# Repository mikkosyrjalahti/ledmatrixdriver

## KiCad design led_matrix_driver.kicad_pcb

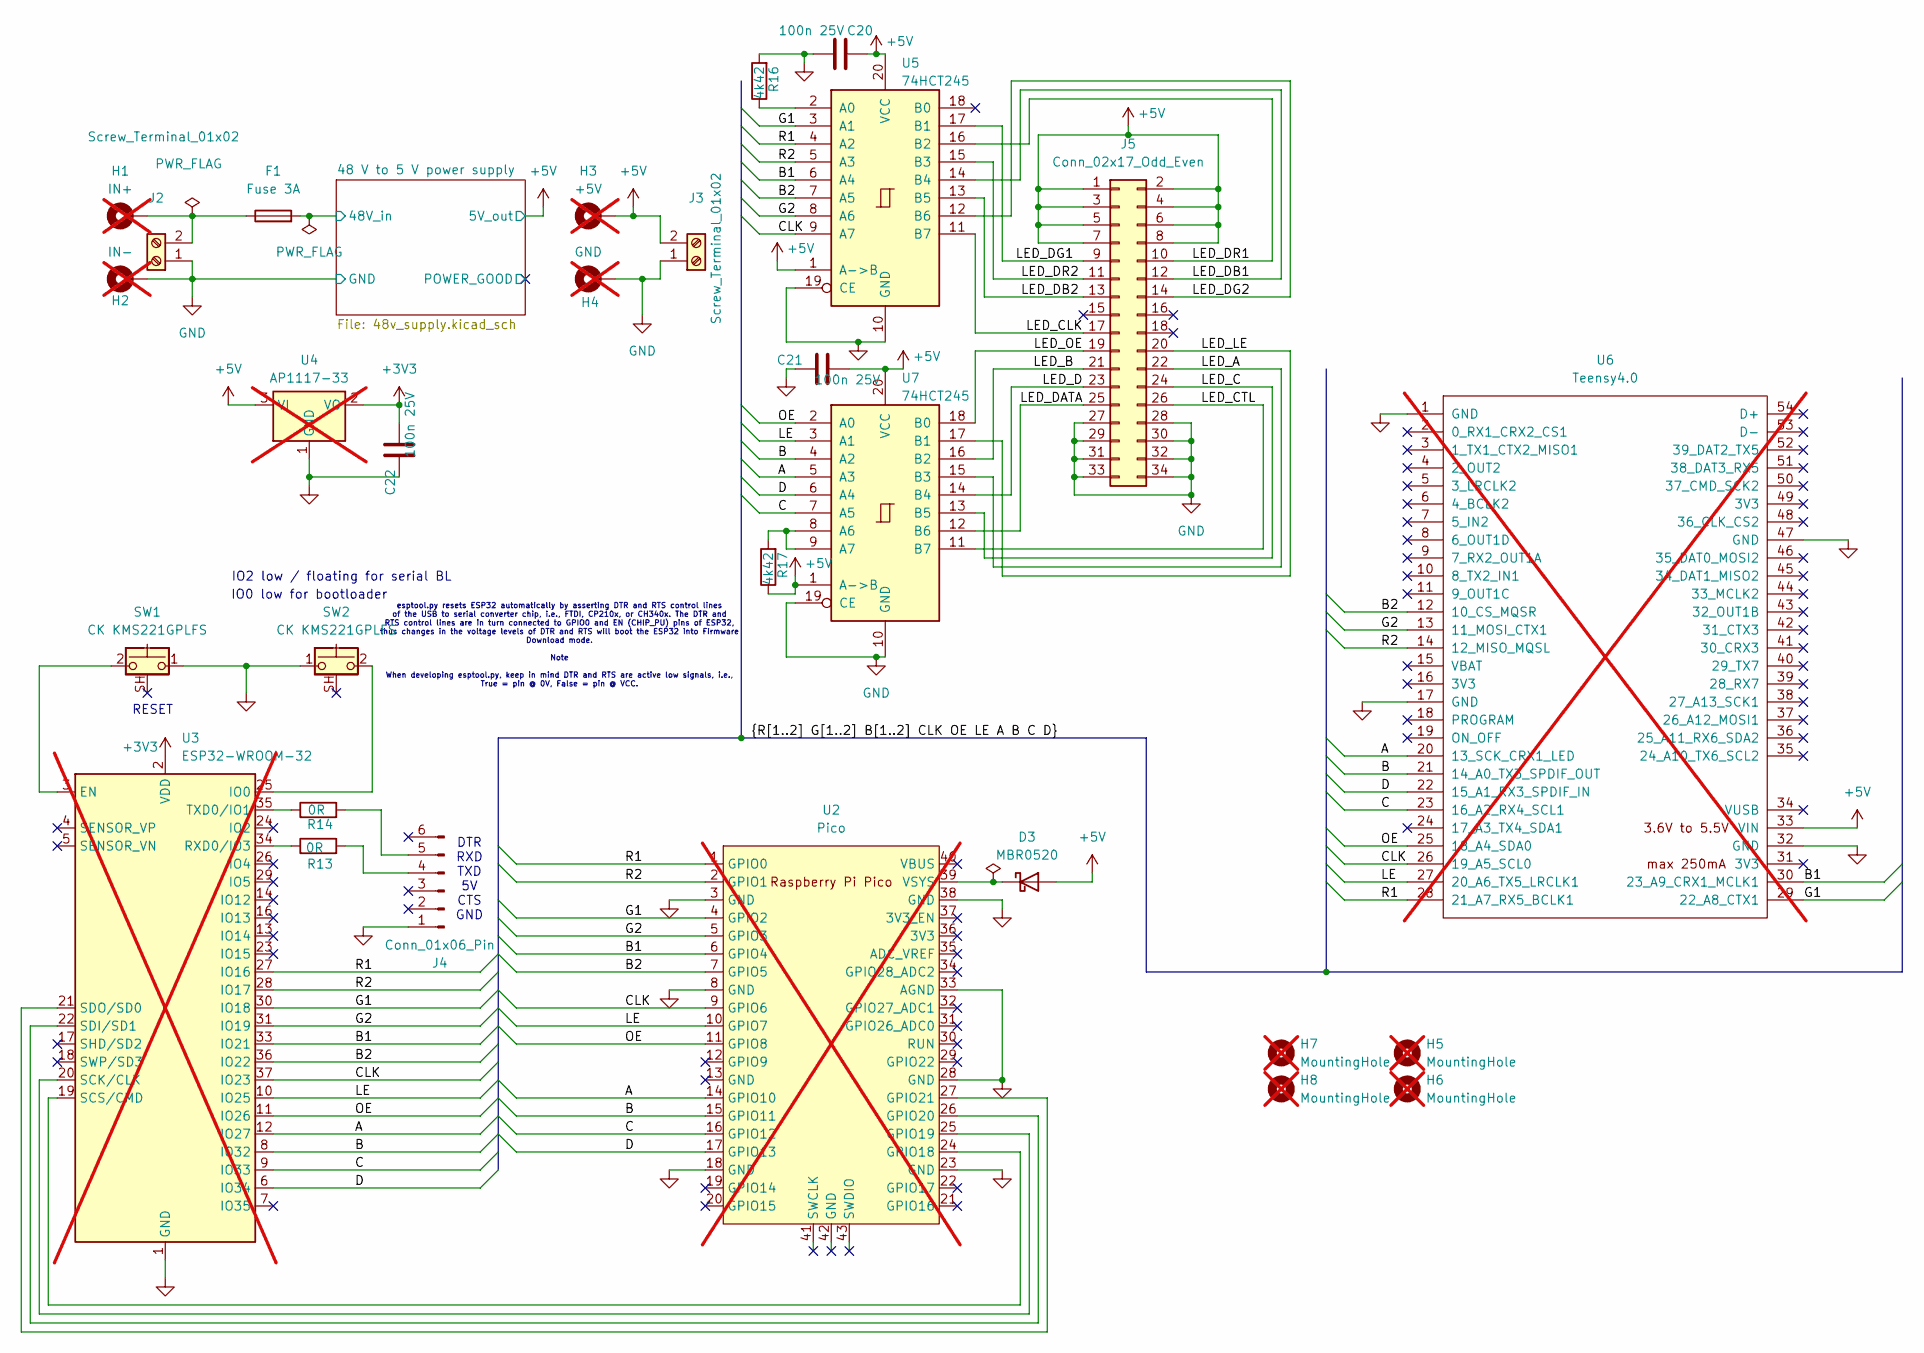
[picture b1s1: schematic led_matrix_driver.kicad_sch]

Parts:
C20, C21, C22: 100n 25V; C_0805_2012Metric; LCSC C28233
D3: MBR0520; D_SOD-123; LCSC C78545
F1: Fuse 3A; Fuseholder_Littelfuse_Nano2_154x; LCSC C206912
H1: IN+; MountingHole_2.2mm_M2_DIN965_Pad; not fitted
H2: IN-; MountingHole_2.2mm_M2_DIN965_Pad; not fitted
H3: +5V; MountingHole_2.2mm_M2_DIN965_Pad; not fitted
H4: GND; MountingHole_2.2mm_M2_DIN965_Pad; not fitted
H5, H6, H7, H8: MountingHole; MountingHole_3.2mm_M3; not fitted
J2, J3: Screw_Terminal_01x02; Samtec_HPM-02-01-x-S_Straight_1x02_Pitch5.08mm
J4: Conn_01x06_Pin; PinHeader_1x06_P2.54mm_Vertical
J5: Conn_02x17_Odd_Even; PinSocket_2x17_P2.54mm_Vertical
R13, R14: 0R; R_0603_1608Metric
R16, R17: 4k42; R_0603_1608Metric; LCSC C2933223
SW1, SW2: CK KMS221GPLFS; SW_SPST_CK_KMS2xxGP
U2: Pico; RPi_Pico_SMD_TH; not fitted
U3: ESP32-WROOM-32; not fitted
U4: AP1117-33; SOT-223-3_TabPin2; not fitted
U5, U7: 74HCT245; SOIC-20W_7.5x12.8mm_P1.27mm; LCSC C94773
U6: Teensy4.0; Teensy40_SMT; not fitted

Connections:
+3V3: C22.2, U3.2 (VDD), U4.2 (VO)
+5V: C20.2, C21.2, D3.2 (A), H3.1, J3.2, J5.1, J5.2, J5.3, J5.4, J5.5, J5.6, J5.7, J5.8, R17.1, U4.3 (VI), U5.1 (A->B), U5.20 (VCC), U6.33 (VIN), U7.1 (A->B), U7.20 (VCC); also elsewhere on the board
/48 V to 5 V power supply/48V_in: F1.2; also elsewhere on the board
/A: U2.14 (GPIO10), U3.12 (IO27), U6.20 (13_SCK_CRX1_LED), U7.5 (A3)
/B: U2.15 (GPIO11), U3.8 (IO32), U6.21 (14_A0_TX3_SPDIF_OUT), U7.4 (A2)
/B1: U2.6 (GPIO4), U3.33 (IO21), U5.6 (A4), U6.30 (23_A9_CRX1_MCLK1)
/B2: U2.7 (GPIO5), U3.36 (IO22), U5.7 (A5), U6.12 (10_CS_MQSR)
/C: U2.16 (GPIO12), U3.9 (IO33), U6.23 (16_A2_RX4_SCL1), U7.7 (A5)
/CLK: U2.9 (GPIO6), U3.37 (IO23), U5.9 (A7), U6.26 (19_A5_SCL0)
/D: U2.17 (GPIO13), U3.6 (IO34), U6.22 (15_A1_RX3_SPDIF_IN), U7.6 (A4)
/G1: U2.4 (GPIO2), U3.30 (IO18), U5.3 (A1), U6.29 (22_A8_CTX1)
/G2: U2.5 (GPIO3), U3.31 (IO19), U5.8 (A6), U6.13 (11_MOSI_CTX1)
/LE: U2.10 (GPIO7), U3.10 (IO25), U6.27 (20_A6_TX5_LRCLK1), U7.3 (A1)
/LED_A: J5.22, U7.15 (B3)
/LED_B: J5.21, U7.16 (B2)
/LED_C: J5.24, U7.13 (B5)
/LED_CLK: J5.17, U5.11 (B7)
/LED_CTL: J5.26, U7.11 (B7)
/LED_D: J5.23, U7.14 (B4)
/LED_DATA: J5.25, U7.12 (B6)
/LED_DB1: J5.12, U5.14 (B4)
/LED_DB2: J5.13, U5.13 (B5)
/LED_DG1: J5.9, U5.17 (B1)
/LED_DG2: J5.14, U5.12 (B6)
/LED_DR1: J5.10, U5.16 (B2)
/LED_DR2: J5.11, U5.15 (B3)
/LED_LE: J5.20, U7.17 (B1)
/LED_OE: J5.19, U7.18 (B0)
/OE: U2.11 (GPIO8), U3.11 (IO26), U6.25 (18_A4_SDA0), U7.2 (A0)
/R1: U2.1 (GPIO0), U3.27 (IO16), U5.4 (A2), U6.28 (21_A7_RX5_BCLK1)
/R2: U2.2 (GPIO1), U3.28 (IO17), U5.5 (A3), U6.14 (12_MISO_MQSL)
GND: C20.1, C21.1, C22.1, H2.1, H4.1, J2.1, J3.1, J4.1, J5.27, J5.28, J5.29, J5.30, J5.31, J5.32, J5.33, J5.34, R16.2, SW1.1, SW2.1, U2.3 (GND), U2.8 (GND), U2.18 (GND), U2.23 (GND), U2.28 (GND), U2.33 (AGND), U2.38 (GND), U3.1 (GND), U3.15 (GND), U3.38 (GND), U3.39 (GND), U4.1 (GND), U5.10 (GND), U5.19 (CE), U6.1 (GND), U6.17 (GND), U6.32 (GND), U6.47 (GND), U7.10 (GND), U7.19 (CE); also elsewhere on the board
unnamed: D3.1 (K), U2.39 (VSYS)
unnamed: F1.1, H1.1, J2.2
unnamed: J4.4, R13.2
unnamed: J4.5, R14.2
unnamed: U2.24 (GPIO18), U3.19 (SCS/CMD)
unnamed: U2.25 (GPIO19), U3.20 (SCK/CLK)
unnamed: U2.26 (GPIO20), U3.22 (SDI/SD1)
unnamed: U2.27 (GPIO21), U3.21 (SDO/SD0)
unnamed: SW1.2, U3.3 (EN)
unnamed: SW2.2, U3.25 (IO0)
unnamed: R13.1, U3.34 (RXD0/IO3)
unnamed: R14.1, U3.35 (TXD0/IO1)
unnamed: R16.1, U5.2 (A0)
unnamed: R17.2, U7.8 (A6), U7.9 (A7)

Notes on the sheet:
DTR RXD TXD 5V CTS GND
IO0 low for bootloader
IO2 low / floating for serial BL
esptool.py resets ESP32 automatically by asserting DTR and RTS control lines of the USB to serial converter chip, i.e., FTDI, CP210x, or CH340x. The DTR and RTS control lines are in turn connected to GPIO0 and EN (CHIP_PU) pins of ESP32, thus changes in the voltage levels of DTR and RTS will boot t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
RESET

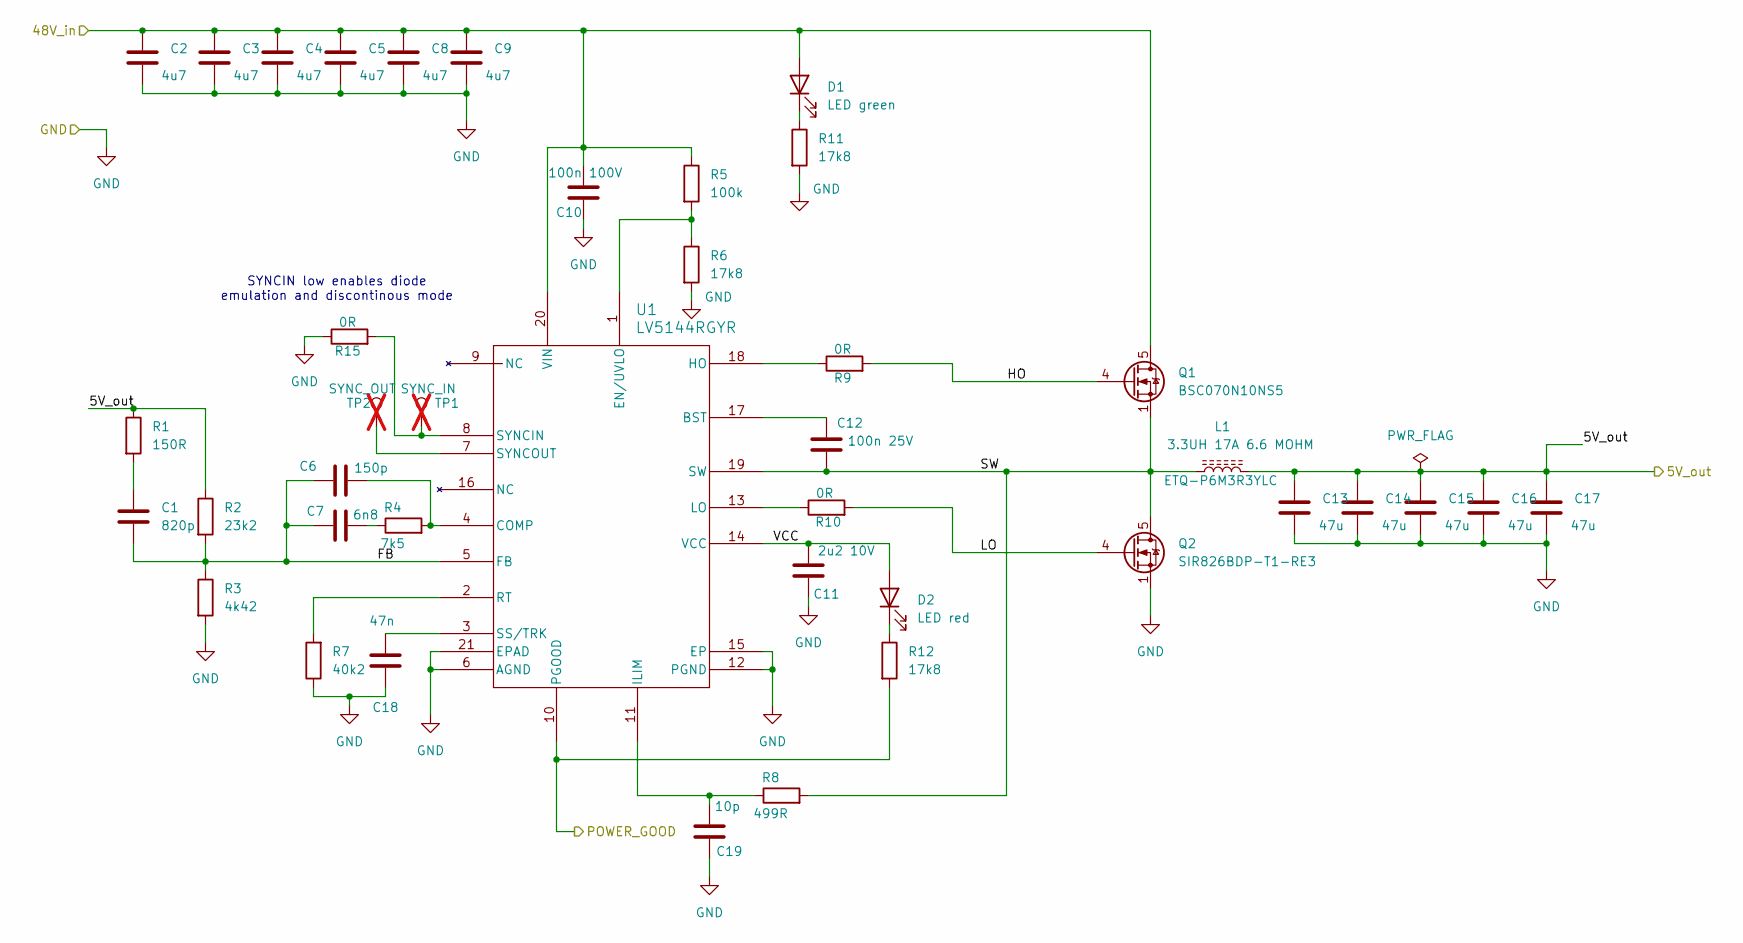
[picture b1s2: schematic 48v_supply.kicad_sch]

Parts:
C1: 820p; C_0603_1608Metric; LCSC C14663
C2, C3, C4, C8, C9: 4u7; C_1210_3225Metric_Pad1.33x2.70mm_HandSolder; MPN GCM32DC72A475KE02L; LCSC C381466
C5: 4u7; C_1210_3225Metric_Pad1.33x2.70mm_HandSolder; LCSC C381466
C6: 150p; C_0603_1608Metric; LCSC C107038
C7: 6n8; C_0603_1608Metric; LCSC C1631
C10: 100n 100V; C_0805_2012Metric; LCSC C28233
C11: 2u2 10V; C_0603_1608Metric; LCSC C23630
C12: 100n 25V; C_0805_2012Metric; LCSC C28233
C13, C14, C15, C16, C17: 47u; C_1210_3225Metric_Pad1.33x2.70mm_HandSolder; MPN JMK325B7476KMHTR; LCSC C77101
C18: 47n; C_0603_1608Metric; LCSC C107093
C19: 10p; C_0603_1608Metric; LCSC C106245
D1: LED green; LED_0805_2012Metric_Pad1.15x1.40mm_HandSolder; LCSC C965815
D2: LED red; LED_0805_2012Metric_Pad1.15x1.40mm_HandSolder; LCSC C94741
L1: 3.3UH 17A 6.6 MOHM; L_Panasonic_PCC-M1060ML; MPN ETQ-P6M3R3YLC; LCSC C149539
Q1: BSC070N10NS5; TDSON-8-1; MPN BSC070N10NS5; LCSC C534364
Q2: SIR826BDP-T1-RE3; TDSON-8-1; MPN TPH4R50ANH1,LQ; LCSC C6296763
R1: 150R; R_0603_1608Metric; LCSC C22808
R2: 23k2; R_0603_1608Metric; LCSC C23346
R3: 4k42; R_0603_1608Metric; LCSC C2933223
R4: 7k5; R_0603_1608Metric; LCSC C114634
R5: 100k; R_0603_1608Metric; LCSC C14675
R6, R11, R12: 17k8; R_0603_1608Metric; LCSC C2933161
R7: 40k2; R_0603_1608Metric; LCSC C2933218
R8: 499R; R_0603_1608Metric; LCSC C23065
R9, R10, R15: 0R; R_0603_1608Metric
TP1: SYNC_IN; TestPoint_Pad_D1.0mm; not fitted
TP2: SYNC_OUT; TestPoint_Pad_D1.0mm; not fitted
U1: LV5144RGYR; VQFN20_RGY_TEX; JLCPCB C34042097

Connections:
+5V: C13.1, C14.1, C15.1, C16.1, C17.1, L1.2, R1.1, R2.1; also elsewhere on the board
/48 V to 5 V power supply/48V_in: C2.1, C3.1, C4.1, C5.1, C8.1, C9.1, C10.2, D1.2 (A), Q1.5 (D), R5.1, U1.20 (VIN); also elsewhere on the board
/48 V to 5 V power supply/FB: C1.2, C6.1, C7.1, R2.2, R3.1, U1.5 (FB)
/48 V to 5 V power supply/HO: Q1.4 (G), R9.2
/48 V to 5 V power supply/LO: Q2.4 (G), R10.2
/48 V to 5 V power supply/POWER_GOOD: R12.2, U1.10 (PGOOD)
/48 V to 5 V power supply/SW: C12.1, L1.1, Q1.1 (S), Q1.2 (S), Q1.3 (S), Q2.5 (D), R8.2, U1.19 (SW)
/48 V to 5 V power supply/VCC: C11.2, D2.2 (A), U1.14 (VCC)
GND: C2.2, C3.2, C4.2, C5.2, C8.2, C9.2, C10.1, C11.1, C13.2, C14.2, C15.2, C16.2, C17.2, C18.1, C19.1, Q2.1 (S), Q2.2 (S), Q2.3 (S), R3.2, R6.2, R7.1, R11.2, R15.1, U1.6 (AGND), U1.12 (PGND), U1.15 (EP), U1.21 (EPAD); also elsewhere on the board
unnamed: C1.1, R1.2
unnamed: C7.2, R4.1
unnamed: D1.1 (K), R11.1
unnamed: D2.1 (K), R12.1
unnamed: C12.2, U1.17 (BST)
unnamed: C6.2, R4.2, U1.4 (COMP)
unnamed: R5.2, R6.1, U1.1 (EN/UVLO)
unnamed: R9.1, U1.18 (HO)
unnamed: C19.2, R8.1, U1.11 (ILIM)
unnamed: R10.1, U1.13 (LO)
unnamed: R7.2, U1.2 (RT)
unnamed: C18.2, U1.3 (SS/TRK)
unnamed: R15.2, TP1.1, U1.8 (SYNCIN)
unnamed: TP2.1, U1.7 (SYNCOUT)

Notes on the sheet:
SYNCIN low enables diode emulation and discontinous mode

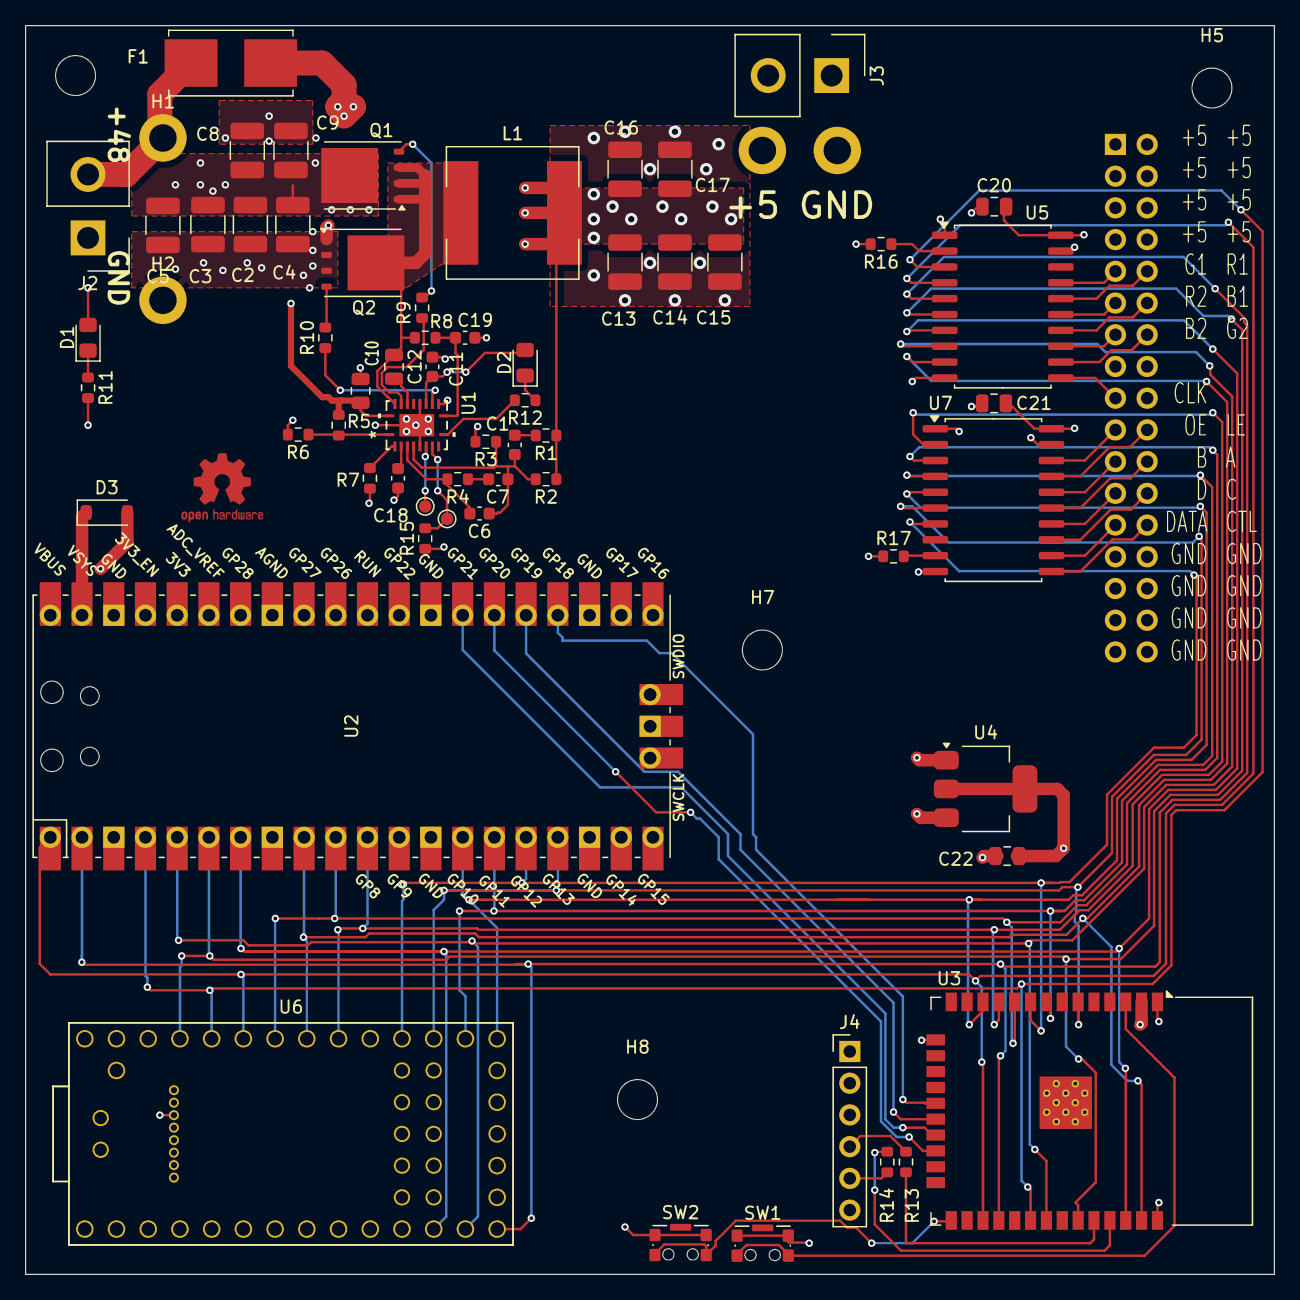
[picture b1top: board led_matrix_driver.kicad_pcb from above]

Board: 4 copper layers, 100.0 x 100.0 mm, 69 parts (1 on the bottom side), 66 nets.

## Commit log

2024-09-25 Initial working version
2024-09-26 Rearranged LED signals for easier layout
2024-09-26 Added Teensy
2024-09-29 Routed data signals. Remove calibration data I2C wires
2024-10-03 Fixed ERC indicated issues. Added ESP32 programming connection.
2024-10-03 Routed rest of the PCB
2024-10-03 DRC fixes
2024-10-03 Added 48V supply sheet
2024-10-03 Updated packages. Added OE to RPi Pico
2024-10-04 Some mounting holes. Release to prod
2024-10-04 Minimum hole size from 0.2 to 0.3mm
2024-10-19 Added DK order numbers
2024-11-27 Minor updates and JLCPCB component codes added
2024-12-02 Added SPI ESP32-Pico. Last component JLCPCB codes
2024-12-17 Corrected HCT245 JLCPCB code. Resulted in HCT244, now HCT245
2026-02-16 Updated .gitignore
2026-02-17 Added comment about 5V direct supply
2026-03-04 Added RP Pico firmware
